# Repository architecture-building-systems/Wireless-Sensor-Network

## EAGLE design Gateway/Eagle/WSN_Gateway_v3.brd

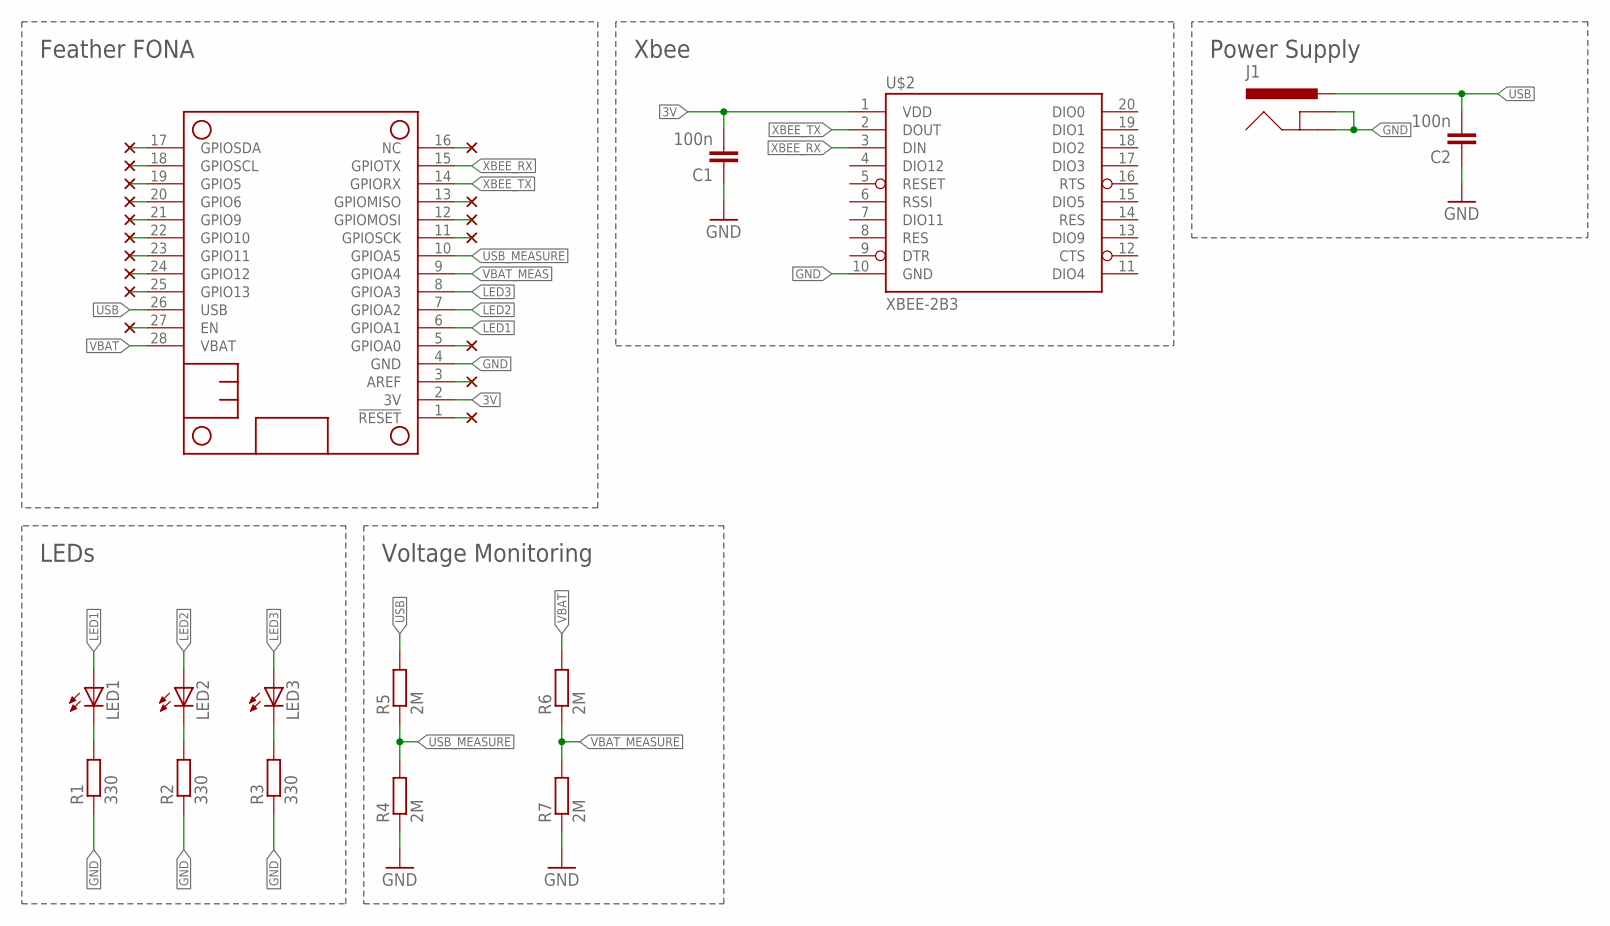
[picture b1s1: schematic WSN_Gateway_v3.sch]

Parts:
C1, C2: 100n; C0805
J1: 5.5x2.1mm Barrel; POWER_JACK_SMD
LED1, LED2, LED3: LEDCHIPLED_0805; CHIPLED_0805
MS1: FEATHERWING_NODIM_NOHOLES; FEATHERWING_DIM_2
R1, R2, R3: 330; R0805
R4, R5, R6, R7: 2M; R0805
U$2: XBEE-2B3; XBEE-SMD

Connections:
3V: C1.2, MS1.2 (3V), U$2.1 (VDD)
GND: C1.1, C2.1, J1.GND (GNDBREAK), J1.P$4 (GND), MS1.4 (GND), R1.1, R2.1, R3.1, R4.1, R7.1, U$2.10 (GND)
LED1: LED1.A, MS1.6 (GPIOA1)
LED2: LED2.A, MS1.7 (GPIOA2)
LED3: LED3.A, MS1.8 (GPIOA3)
unnamed: LED1.C, R1.2
unnamed: LED2.C, R2.2
unnamed: LED3.C, R3.2
USB: C2.2, J1.VIN0 (PWR), J1.VIN1 (PWR), MS1.26 (USB), R5.2
USB_MEASURE: MS1.10 (GPIOA5), R4.2, R5.1
VBAT: MS1.28 (VBAT), R6.2
VBAT_MEAS: MS1.9 (GPIOA4)
VBAT_MEASURE: R6.1, R7.2
XBEE_RX: MS1.15 (GPIOTX), U$2.3 (DIN)
XBEE_TX: MS1.14 (GPIORX), U$2.2 (DOUT)

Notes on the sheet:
Xbee
Feather FONA
LEDs
Power Supply
Voltage Monitoring

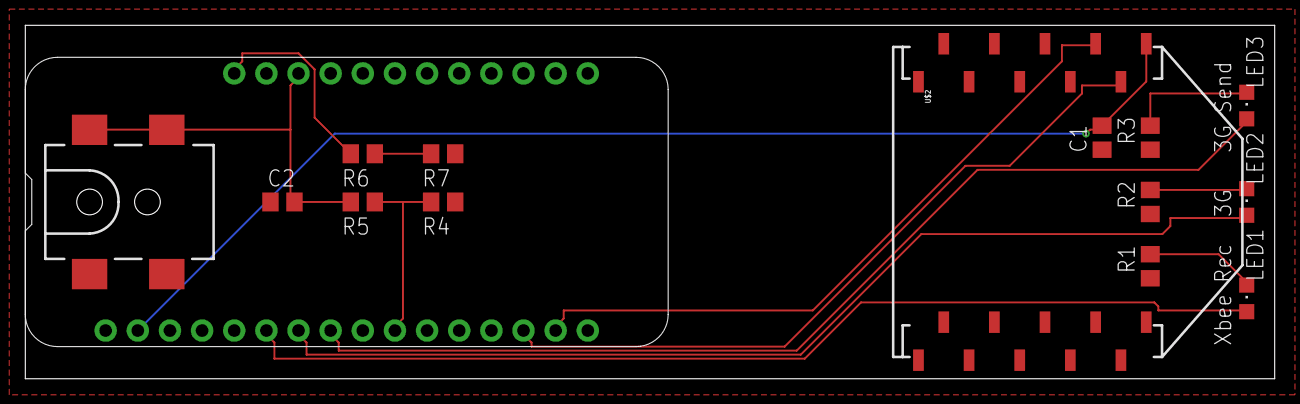
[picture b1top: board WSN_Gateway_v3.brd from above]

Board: 2 copper layers, 98.7 x 27.9 mm, 15 parts (0 on the bottom side), 14 nets.

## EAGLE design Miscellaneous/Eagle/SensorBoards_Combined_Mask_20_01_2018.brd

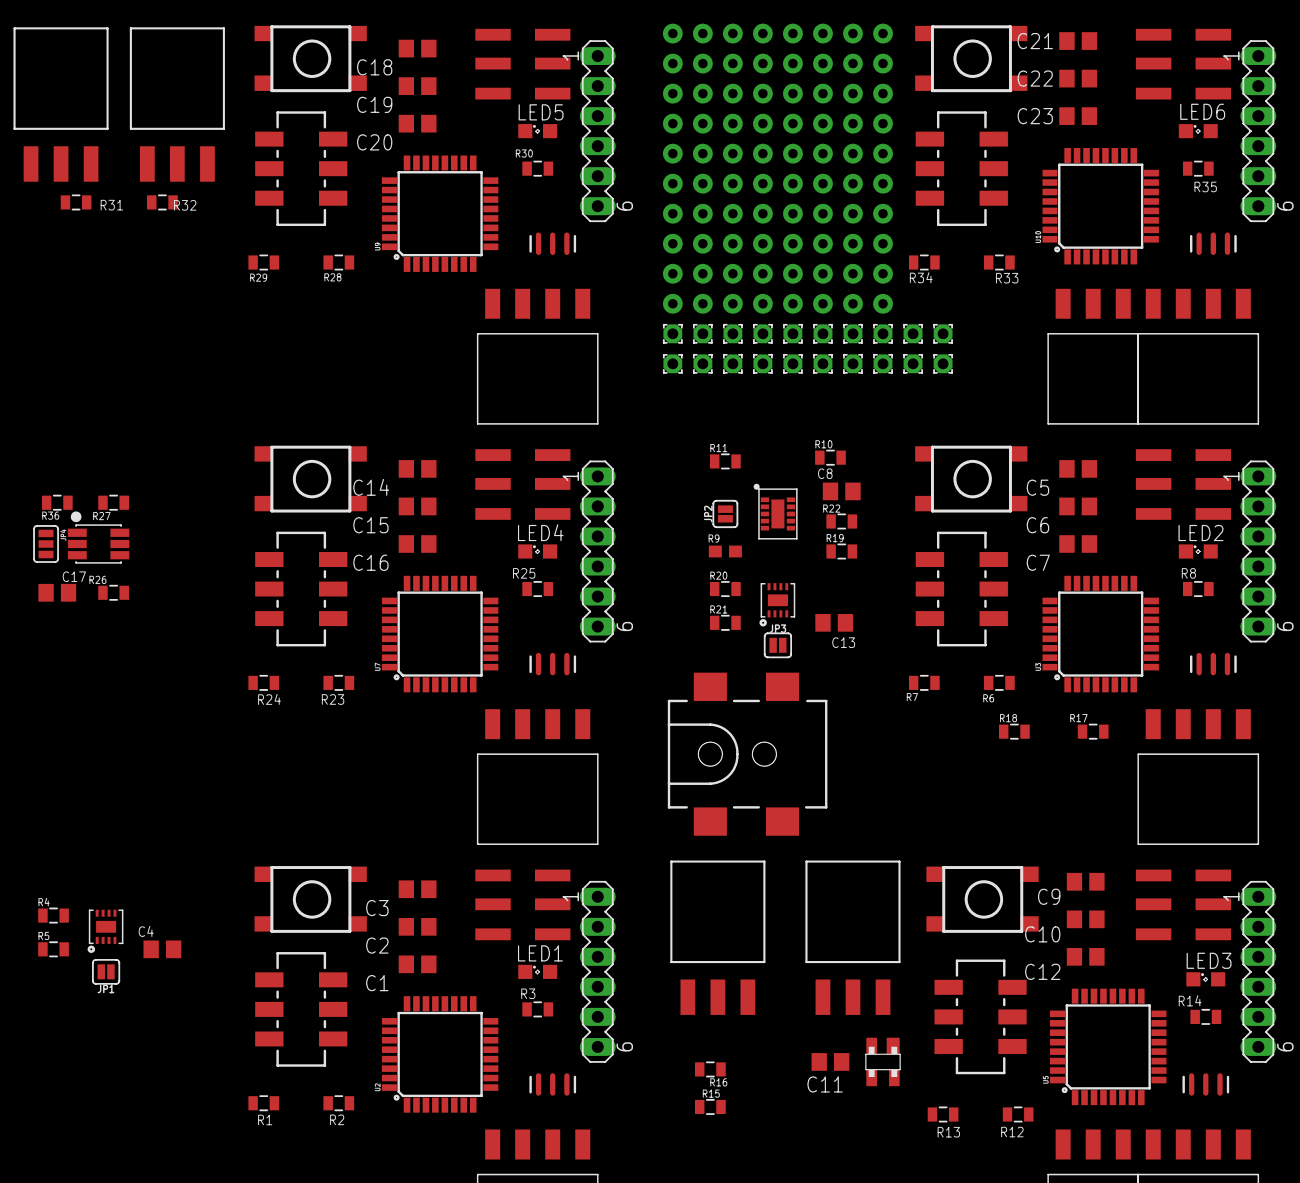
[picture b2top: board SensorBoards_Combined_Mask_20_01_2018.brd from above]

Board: 2 copper layers, 144 parts (0 on the bottom side), 141 nets, no tracks yet.

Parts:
C1, C2, C3, C4, C5, C6, C7, C8, C9, C10, C11, C12, C13, C14, C15, C16, C17, C18, C19, C20, C21, C22, C23: 100n; C0805
J1, J3, J7, J12: M04_SMD_90
J2, J4, J6, J8, J11: ARDUINO_ISP; M-2X3
J5: 5.5x2.1mm Barrel; POWER_JACK_SMD
J9, J10: 1x3 RA Female .1"; 1X03_SMD_RA_FEMALE
JP1, JP2, JP3: SPARKFUN-JUMPERS_SMT-JUMPER_2_NO_SILK
JP4: MIKE-TEMP_SJ_3
LED1, LED2, LED3, LED4, LED5, LED6: Red; SML0805
PAD1, PAD2, PAD3, PAD4, PAD5, PAD6, PAD7, PAD8, PAD9, PAD10, PAD11, PAD12, PAD13, PAD14, PAD15, PAD16, PAD17, PAD18, PAD19, PAD20: 1,6/0,9
R1, R2, R4, R6, R7, R10, R12, R13, R15, R16, R17, R18, R19, R20, R23, R24, R26, R27, R28, R29, R33, R34, R36: 10k; 0805
R3, R8, R14, R25, R30, R35: 330; 0805
R5, R11, R21, R22: 100k; 0805
R9: 10k; CCS811_BREAKOUT_TEMP_0603
R31, R32: 4.7k; 0805
S1, S2, S5, S7, S9, S11: Reset; M-PUSHBUTTON-SMD
S3, S4, S6, S8, S10, S12: JS202011SCQN
SV1, SV2, SV8, SV9, SV10, SV11: MA06-1
SV3: M03_SMD_90
SV4, SV5: 1x3 RA Female .1"; 1X03_SMD_RA_FEMALE
SV6: ARDUINO_ISP; M-2X3
SV7: M04_SMD_90
U1, U6: MICROBUILDER_SHT3X
U2, U3, U5, U7, U9, U10: ATMEGA328P_TQFP; TQFP32-08
U4: CCS811; CCS811_BREAKOUT_TEMP_LGA10
U8: MIKE-TEMP_TSL2561T; MIKE-TEMP_TMB-6
U$1: M04_SMD_90
U$2: MAX6816EUS; SOT143
U$3: M03_SMD_90
U$4: 10X8_PROTOTYPE_AREA
Y1, Y2, Y3, Y4, Y5, Y6: 8MHZ; RESONATOR-SMD

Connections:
+5V: PAD19.1, PAD20.1, U$3.3
ADC6: PAD3.1, PAD12.1, U10.19
ADC7: PAD4.1, PAD13.1, U10.22
AUX: R9.1, R19.1, U4.8
DBG_ENABLE: R1.2, U2.26
DBG_ENABLE1: R7.2, U3.26
DBG_ENABLE2: R13.2, U5.26
DBG_ENABLE3: R24.2, U7.26
DBG_ENABLE4: R29.2, U9.26
DBG_ENABLE5: R34.2, U10.26
DIGITAL_INPUT_1: U5.32, U$2.OUT
DIGITAL_INPUT_2: R15.1, R16.1, SV5.2, U5.1
DS18B20_DATA_1: J10.2, R31.1, U9.32
DS18B20_DATA_2: J9.2, R32.1, U9.1
FTDI_RESET: C1.1, SV1.6
FTDI_RESET1: C7.1, SV2.6
FTDI_RESET2: C12.1, SV8.6
FTDI_RESET3: C16.1, SV9.6
FTDI_RESET4: C20.1, SV10.6
FTDI_RESET5: C23.1, SV11.6
FTDI_RXI: SV1.4, U2.30
FTDI_RXI1: SV2.4, U3.30
FTDI_RXI2: SV8.4, U5.30
FTDI_RXI3: SV9.4, U7.30
FTDI_RXI4: SV10.4, U9.30
FTDI_RXI5: SV11.4, U10.30
FTDI_TXO: SV1.5, U2.31
FTDI_TXO1: SV2.5, U3.31
FTDI_TXO2: SV8.5, U5.31
FTDI_TXO3: SV9.5, U7.31
FTDI_TXO4: SV10.5, U9.31
FTDI_TXO5: SV11.5, U10.31
GND: C2.2, C3.2, C4.2, J1.4, J4.P$5, JP1.1, LED1.C, S1.1, S1.2, S3.3, SV1.1, SV1.2, U1.7, U1.8, U1.THERMAL, U2.3, U2.5, U2.21, Y1.2
GND1: C5.2, C6.2, C8.2, C13.2, J2.P$5, J3.4, J5.GND, J5.P$4, JP2.1, JP3.1, LED2.C, R22.1, S2.1, S2.2, S4.3, SV2.1, SV2.2, U3.3, U3.5, U3.21, U4.EP, U6.7, U6.8, U6.THERMAL, Y2.2
GND2: C9.2, C10.2, LED3.C, R15.2, S5.1, S5.2, S6.3, SV4.1, SV5.3, SV6.P$5, SV7.4, SV8.1, SV8.2, U5.3, U5.5, U5.21, U$2.GND, Y3.2
GND3: C14.2, C15.2, C17.1, J6.P$5, J7.4, JP4.3, LED4.C, S7.1, S7.2, S8.3, SV9.1, SV9.2, U7.3, U7.5, U7.21, U8.3, Y4.2
GND4: C18.2, C19.2, J8.P$5, J9.1, J10.1, LED5.C, S9.1, S9.2, S10.3, SV10.1, SV10.2, U9.3, U9.5, U9.21, U$1.4, Y5.2
GND5: C21.2, C22.2, J11.P$5, J12.4, LED6.C, S11.1, S11.2, S12.3, SV11.1, SV11.2, U10.3, U10.5, U10.21, U$3.1, U$4.P$1, U$4.P$2, U$4.P$3, U$4.P$4, U$4.P$5, U$4.P$6, U$4.P$7, U$4.P$8, Y6.2
INT0: PAD6.1, PAD15.1, U10.32
INT_TO_COM: SV3.1, U5.2
L1: R3.2, U2.14
L2: R8.2, U3.14
L3: R14.2, U5.14
L4: R25.2, U7.14
L5: R30.2, U9.14
L6: R35.2, U10.14
MCU_RXI: J1.3, U2.11
MCU_RXI1: J3.3, U3.11
MCU_RXI2: SV7.3, U5.11
MCU_RXI3: J7.3, U7.11
MCU_RXI4: U9.11, U$1.3
MCU_RXI5: J12.3, U10.11
MCU_TXO: J1.2, U2.10
MCU_TXO1: J3.2, U3.10
MCU_TXO2: SV7.2, U5.10
MCU_TXO3: J7.2, U7.10
MCU_TXO4: U9.10, U$1.2
MCU_TXO5: J12.2, U10.10
MISO: J4.P$1, U2.16
MISO1: J2.P$1, U3.16
MISO2: SV6.P$1, U5.16
MISO3: J6.P$1, U7.16
MISO4: J8.P$1, U9.16
MISO5: J11.P$1, U10.16
MOSI: J4.P$3, U2.15
MOSI1: J2.P$3, U3.15
MOSI2: SV6.P$3, U5.15
MOSI3: J6.P$3, U7.15
MOSI4: J8.P$3, U9.15
MOSI5: J11.P$3, U10.15
unnamed: U2.8, Y1.3
unnamed: U2.7, Y1.1
unnamed: R1.1, S3.2
unnamed: R4.1, U1.6
unnamed: JP1.2, R5.1, U1.2
unnamed: U3.8, Y2.3
unnamed: U3.7, Y2.1
unnamed: LED2.A, R8.1
unnamed: C5.1, U3.20
unnamed: R7.1, S4.2
unnamed: JP2.2, R11.1, U4.1
unnamed: R20.1, U6.6
unnamed: U5.8, Y3.3
unnamed: U5.7, Y3.1
unnamed: C3.1, U2.20
unnamed: LED3.A, R14.1
unnamed: C9.1, U5.20
unnamed: SV4.2, U$2.IN
unnamed: R13.1, S6.2
unnamed: JP3.2, R21.1, U6.2
unnamed: R22.2, U4.7
unnamed: U7.8, Y4.3
unnamed: U7.7, Y4.1
unnamed: LED4.A, R25.1
unnamed: C14.1, U7.20
unnamed: R24.1, S8.2
unnamed: JP4.1, R36.1
unnamed: U9.8, Y5.3
unnamed: U9.7, Y5.1
unnamed: LED1.A, R3.1
unnamed: LED5.A, R30.1
unnamed: C18.1, U9.20
unnamed: R29.1, S10.2
unnamed: U10.8, Y6.3
unnamed: U10.7, Y6.1
unnamed: LED6.A, R35.1
unnamed: C21.1, U10.20
unnamed: R34.1, S12.2
unnamed: JP4.2, U8.2
NTC_SENSE: R9.2, U4.4, U4.5
PC0: PAD7.1, PAD16.1, U10.23
PC1: PAD8.1, PAD17.1, U10.24
PC2: PAD9.1, PAD18.1, U10.25
RESET: C1.2, J4.P$4, R2.1, S1.3, S1.4, U2.29
RESET1: C7.2, J2.P$4, R6.1, S2.3, S2.4, U3.29
RESET2: C12.2, R12.1, S5.3, S5.4, SV6.P$4, U5.29
RESET3: C16.2, J6.P$4, R23.1, S7.3, S7.4, U7.29
RESET4: C20.2, J8.P$4, R28.1, S9.3, S9.4, U9.29
RESET5: C23.2, J11.P$4, R33.1, S11.3, S11.4, U10.29
SCK: J4.P$2, U2.17
SCK1: J2.P$2, U3.17
SCK2: SV6.P$2, U5.17
SCK3: J6.P$2, U7.17
SCK4: J8.P$2, U9.17
SCK5: J11.P$2, U10.17
SCL: U1.4, U2.28
SCL1: R18.1, U3.28, U4.10, U6.4
SCL2: R26.1, U7.28, U8.4
SCL3: PAD2.1, PAD11.1, U10.28
SDA: U1.1, U2.27
SDA1: R17.1, U3.27, U4.9, U6.1
SDA2: R27.1, U7.27, U8.6
SDA3: PAD1.1, PAD10.1, U10.27
SENS_RES: R10.1, U4.2
VCC: C2.1, C4.1, J1.1, J4.P$6, R2.2, R4.2, R5.2, S3.1, SV1.3, U1.5, U2.4, U2.6, U2.18
VCC1: C6.1, C8.1, C13.1, J2.P$6, J3.1, J5.VIN0, J5.VIN1, R6.2, R10.2, R11.2, R17.2, R18.2, R19.2, R20.2, R21.2, S4.1, SV2.3, U3.4, U3.6, U3.18, U4.6, U6.5
VCC2: C10.1, R12.2, R16.2, S6.1, SV5.1, SV6.P$6, SV7.1, SV8.3, U5.4, U5.6, U5.18
VCC3: C15.1, C17.2, J6.P$6, J7.1, R23.2, R26.2, R27.2, R36.2, S8.1, SV9.3, U7.4, U7.6, U7.18, U8.1
VCC4: C19.1, J8.P$6, J9.3, J10.3, R28.2, R31.2, R32.2, S10.1, SV10.3, U9.4, U9.6, U9.18, U$1.1
VCC5: C22.1, J11.P$6, J12.1, PAD5.1, PAD14.1, R33.2, S12.1, SV11.3, U10.4, U10.6, U10.18, U$3.2
VDD: C11.1, SV3.2, U$2.VCC

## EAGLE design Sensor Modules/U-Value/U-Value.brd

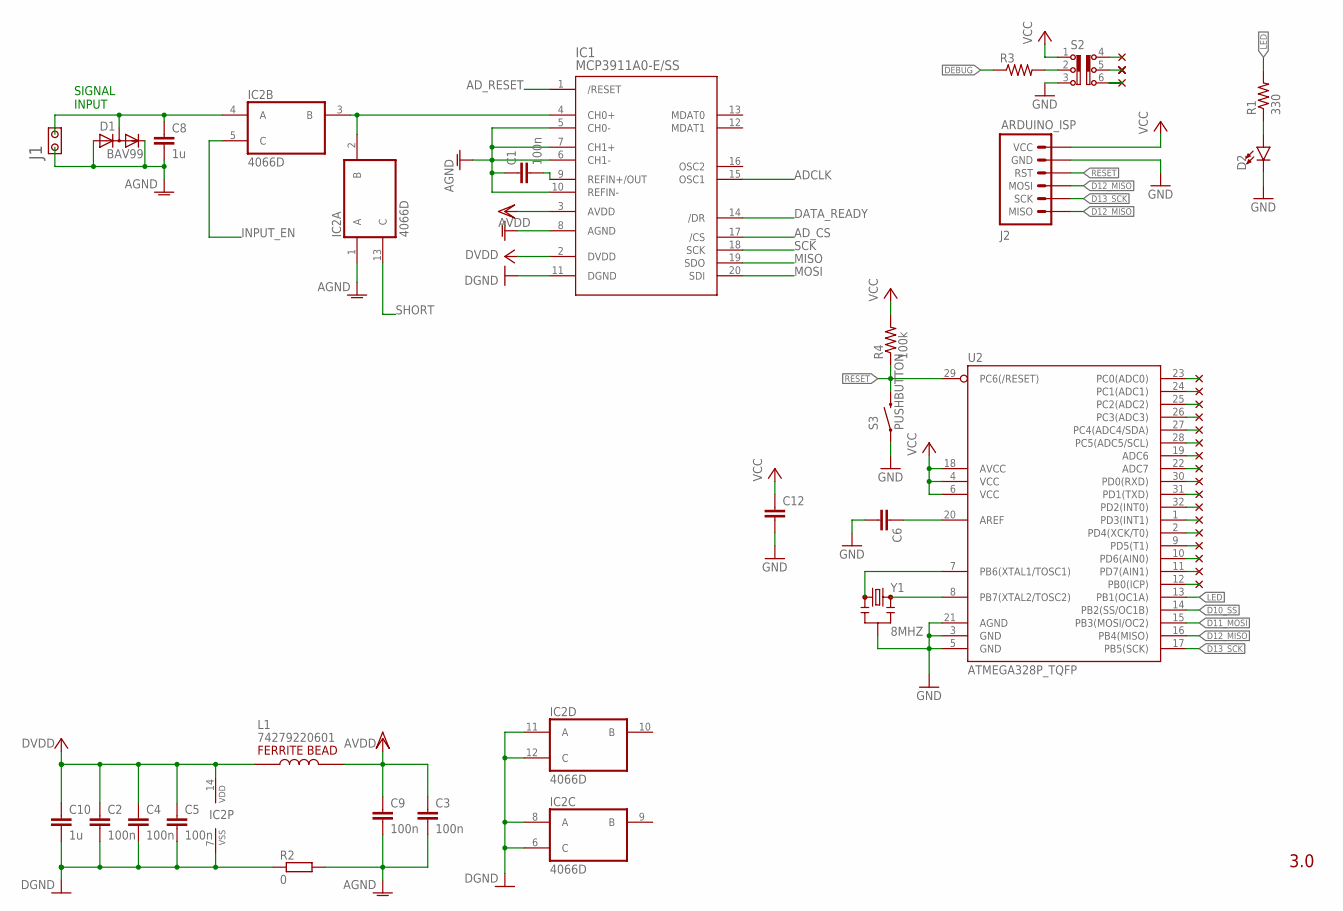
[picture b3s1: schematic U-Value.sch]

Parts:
C1, C2, C3, C4, C5, C9: 100n; C0805
C6, C12: CAP0805; 0805
C8, C10: 1u; C0805
D1: BAV99; SOT23
D2: LED0603; LED-0603
IC1: MCP3911A0-E/SS; SSOP20
IC2: 4066D; SO14
J1: CON2X1
J2: ARDUINO_ISP; M-2X3
L1: 74279220601; 0805
R1: 330; 0805
R2: 0; M0805
R3: RESISTOR0805-RES; 0805
R4: 100k; 0805
S2: SLIDE_SWITCH_JS202011SCQN; JS202011SCQN
S3: PUSHBUTTON; M-PUSHBUTTON-SMD
U2: ATMEGA328P_TQFP; TQFP32-08
Y1: 8MHZ; RESONATOR-SMD

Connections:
ADCLK: IC1.15 (OSC1)
AD_CS: IC1.17 (/CS)
AD_RESET: IC1.1 (/RESET)
AGND: C1.1, C3.2, C8.2, C9.2, D1.1 (A), D1.2 (C), IC1.5 (CH0-), IC1.6 (CH1-), IC1.7 (CH1+), IC1.8 (AGND), IC1.10 (REFIN-), IC2.1 (A), J1.1, R2.2
AVDD: C3.1, C9.1, IC1.3 (AVDD), L1.2
D10_SS: U2.14 (PB2(SS/OC1B))
D11_MOSI: U2.15 (PB3(MOSI/OC2))
D12_MISO: J2.P$1 (MISO), J2.P$3 (MOSI), U2.16 (PB4(MISO))
D13_SCK: J2.P$2 (SCK), U2.17 (PB5(SCK))
DATA_READY: IC1.14 (/DR)
DEBUG: R3.1
DGND: C2.2, C4.2, C5.2, C10.2, IC1.11 (DGND), IC2.6 (C), IC2.7 (VSS), IC2.8 (A), IC2.11 (A), IC2.12 (C), R2.1
DVDD: C2.1, C4.1, C5.1, C10.1, IC1.2 (DVDD), IC2.14 (VDD), L1.1
GND: C6.2, C12.2, D2.C, J2.P$5 (GND), S2.3, S3.1 (LEFT), S3.2 (LEFT), U2.3 (GND), U2.5 (GND), U2.21 (AGND), Y1.2
INPUT_EN: IC2.5 (C)
LED: R1.2, U2.13 (PB1(OC1A))
MISO: IC1.19 (SDO)
MOSI: IC1.20 (SDI)
unnamed: C1.2, IC1.9 (REFIN+/OUT)
unnamed: C6.1, U2.20 (AREF)
unnamed: IC1.4 (CH0+), IC2.2 (B), IC2.3 (B)
unnamed: C8.1, D1.3 (AC), IC2.4 (A), J1.2
unnamed: U2.8 (PB7(XTAL2/TOSC2)), Y1.3
unnamed: D2.A, R1.1
unnamed: U2.7 (PB6(XTAL1/TOSC1)), Y1.1
unnamed: R3.2, S2.2
RESET: J2.P$4 (RST), R4.1, S3.3 (RIGHT), S3.4 (RIGHT), U2.29 (PC6(/RESET))
SCK: IC1.18 (SCK)
SHORT: IC2.13 (C)
VCC: C12.1, J2.P$6 (VCC), R4.2, S2.1, U2.4 (VCC), U2.6 (VCC), U2.18 (AVCC)

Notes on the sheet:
SIGNAL INPUT
3.0

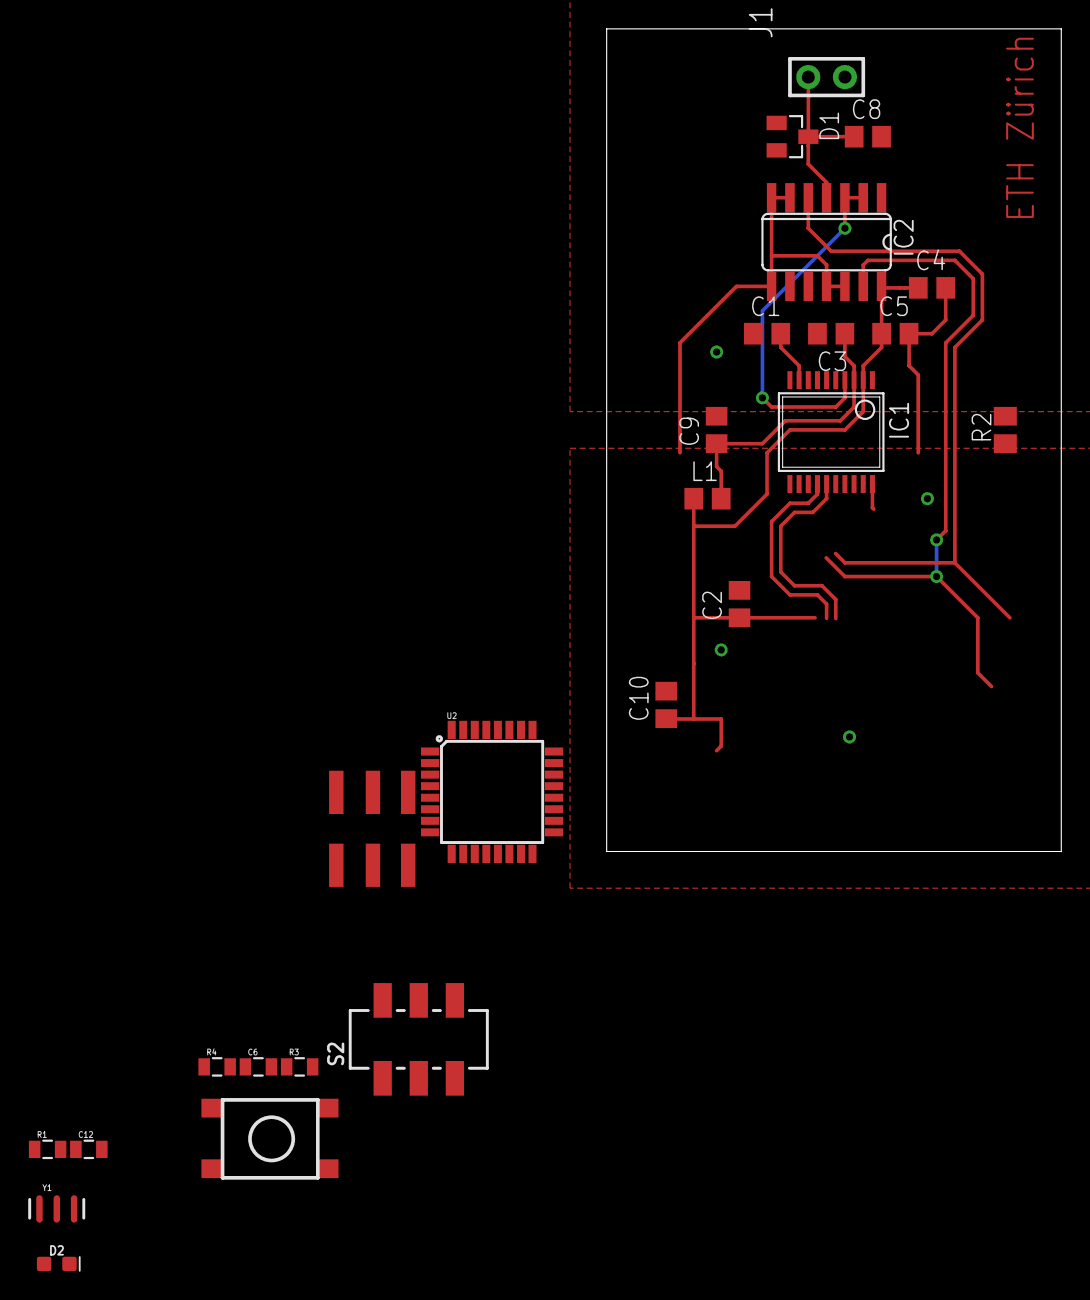
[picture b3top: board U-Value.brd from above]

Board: 2 copper layers, 31.5 x 57.0 mm, 25 parts (0 on the bottom side), 18 nets.

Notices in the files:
parts and their libraries:
SparkFun-RF: Licensing: Creative Commons ShareAlike 4.0 International - https://creativecommons.org/licenses/by-sa/4.0
